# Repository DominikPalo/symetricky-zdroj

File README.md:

# Miniatúrny symetrický zdroj +/-5V, +/-12V s ochranou proti skratu

Repozitár obsahuje všetky potrebné iformácie k stavbe zdroja. Autorom elektro dizajnu (DPS a schéma) je David Čada (alias Davidus / Drirr90). Nakoľko sa jedná o šikovný zdroj pre domáce použite, v tomto repozitári nájdete dokumentáciu a materiály, ktoré som vytvoril pri jeho konštrukcii. Video s podrobným opisom zdroja nájdete na: https://youtu.be/iAIXDw9BsSQ.

## Obsah repozitára
1. Pôvodná schéma zapojenia a PCB vo formáte EAGLE (autor: David Čada)
1. Gerber súbory potrebné k výrobe DPS (JLCPCB, PCBWay, ...)
1. [Zoznam použitých komponentov (BOM)](BOM.md) aj s odkazmi na distribútorov TME a GME
1. 3D model krabičky na zdroj vhodný k tlači na 3D tlačiarni
1. Fotodokumetáciu mojej konštrukcie (pridám neskôr)

## Info od autora eletkro dizajnu:
>1. Pouze k nekomercnimu pouziti.
>1. Pokud chcete prezentovat zdroj i jinde, tak pouze s temito podminkami pouziti + odkaz na zdroj https://youtu.be/iAIXDw9BsSQ
>1. Rad zodpovim jakekoli dotazy na adrese cada.david zavinac gmail.com

## 3D krabička

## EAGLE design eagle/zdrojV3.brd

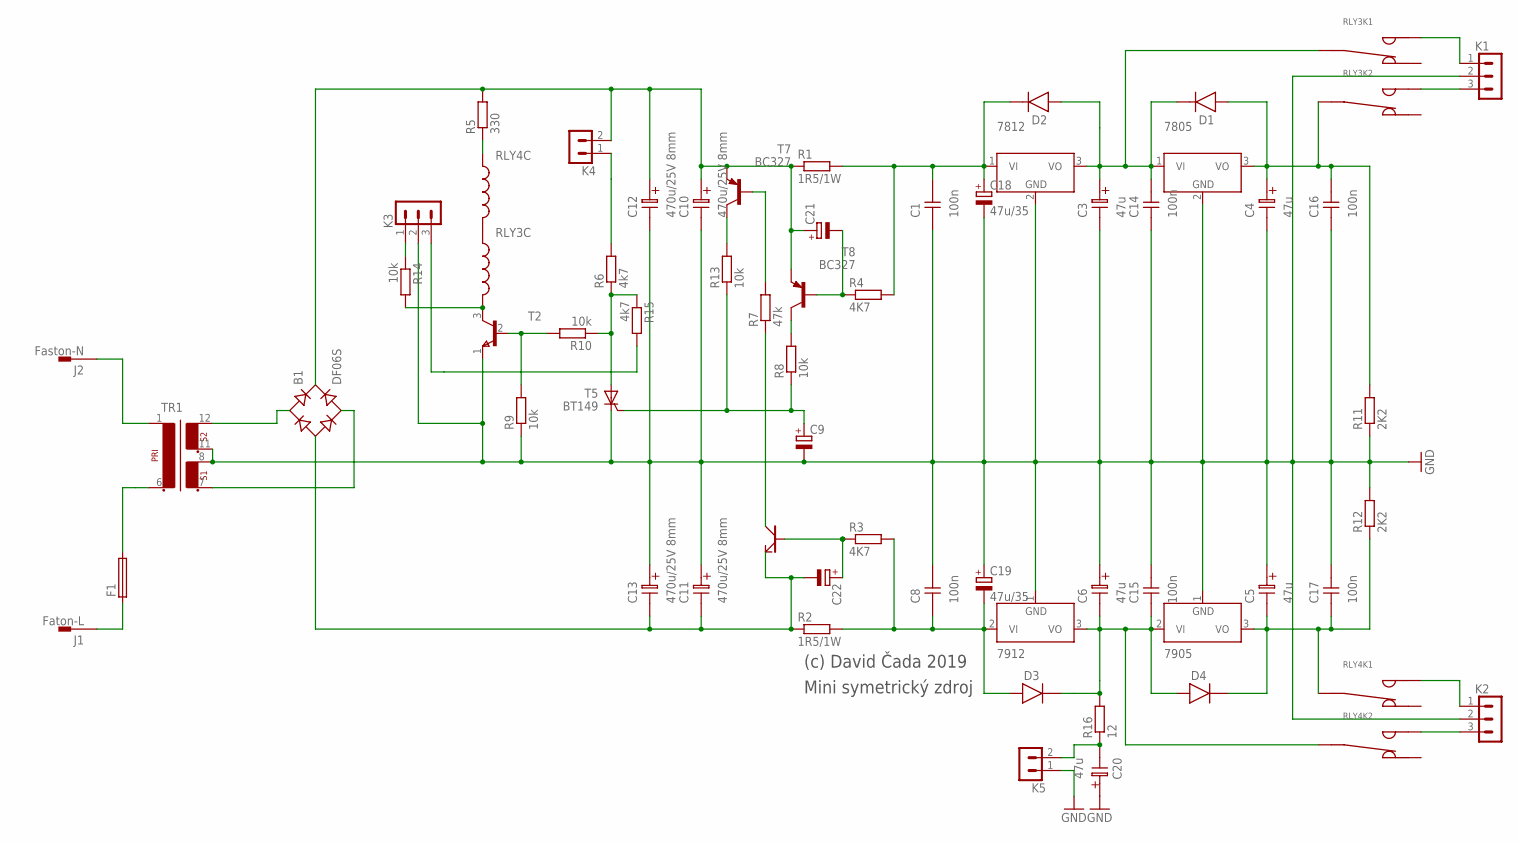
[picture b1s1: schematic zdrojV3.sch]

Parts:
7805: 7812; TO-220S
7812: 7805; TO-220S
7905: 7912; TO-220S
7912: 7905; TO-220S
B1: DF06S; DFS
C1, C8, C14, C15, C16, C17: 100n; CK
C3, C4, C5, C6, C20: 47u; CT12
C9, C21, C22: CPOL-EUE2.5-6; E2,5-6
C10, C11, C12, C13: 470u/25V 8mm; CT12
C18, C19: 47u/35; E2,5-6
D1, D2, D3, D4: 1N4007; DO41
F1: 19560
J1: Faton-L; F061.100
J2: Faston-N; F061.100
K1, K2, K3: PSH02-03P
K4, K5: PSH02-02P
R1, R2: 1R5/1W; 0411V
R3, R4: 4K7; 0207/2V
R5: 330; 0207/2V
R6, R15: 4k7; 0207/2V
R7: 47k; 0207/2V
R8, R9, R10, R13, R14: 10k; 0207/2V
R11, R12: 2K2; 0207/2V
R16: 12; 0207/2V
RLY3, RLY4: RELEG5V2; RG5V2
T2: BC337-40; TO-92C
T5: BT149; TO92-4
T6: MPSA44; TO92-EBC
T7, T8: BC327; TO92
TR1: EI48-2

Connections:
GND: 7805.2 (GND), 7812.2 (GND), 7905.1 (GND), 7912.1 (GND), C1.1, C3.2, C4.2, C5.1, C6.1, C8.2, C9.-, C10.2, C11.1, C12.2, C13.1, C14.1, C15.2, C16.1, C17.2, C18.-, C19.+, C20.1, K1.2, K2.2, K3.2, K5.1, R9.1, R11.1, R12.2, T2.1 (E), T5.C, TR1.8 (4), TR1.11 (5)
LEDGREEN+: K3.3, R15.2
unnamed: R7.2, T7.2 (B)
unnamed: 7805.1 (VI), 7812.3 (VO), C3.1, C14.2, D1.K, D2.A, RLY3.3
unnamed: 7905.2 (VI), 7912.3 (VO), C6.2, C15.1, D3.K, D4.A, R16.2, RLY4.6 (3)
unnamed: 7912.2 (VI), C8.1, C19.-, D3.A, R2.2, R3.2
unnamed: 7812.1 (VI), C1.2, C18.+, D2.K, R1.2, R4.2
unnamed: K1.1, RLY3.5 (1)
unnamed: 7905.3 (VO), C5.2, C17.1, D4.K, R12.1, RLY4.3
unnamed: R13.2, T7.3 (C)
unnamed: R9.2, R10.2, T2.2 (B)
unnamed: C22.+, R3.1, T6.B
unnamed: C21.-, R4.1, T8.2 (B)
unnamed: RLY3.1, RLY4.2
unnamed: R5.1, RLY4.1
unnamed: C9.+, R8.1, R13.1, T5.G
unnamed: R6.1, R10.1, R15.1, T5.A
unnamed: R14.2, RLY3.2, T2.3 (C)
unnamed: K4.1, R6.2
unnamed: K3.1, R14.1
unnamed: R7.1, T6.E (C)
unnamed: R8.2, T8.3 (C)
unnamed: F1.2, TR1.6 (2)
unnamed: B1.+, C10.1, C12.1, C21.+, K4.2, R1.1, R5.2, T7.1 (E), T8.1 (E)
unnamed: B1.AC1, TR1.12 (6)
unnamed: B1.AC2, TR1.7 (3)
unnamed: 7805.3 (VO), C4.1, C16.2, D1.A, R11.2, RLY3.6 (3)
unnamed: B1.-, C11.2, C13.2, C22.-, R2.1, T6.C (E)
unnamed: K1.3, RLY3.8 (1)
unnamed: K2.1, RLY4.5 (1)
unnamed: K2.3, RLY4.8 (1)
unnamed: C20.2, K5.2, R16.1
unnamed: J2.A1, J2.A2, TR1.1
POJISTKA: F1.1, J1.A1, J1.A2

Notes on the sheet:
(c) David Čada 2019
Mini symetrický zdroj

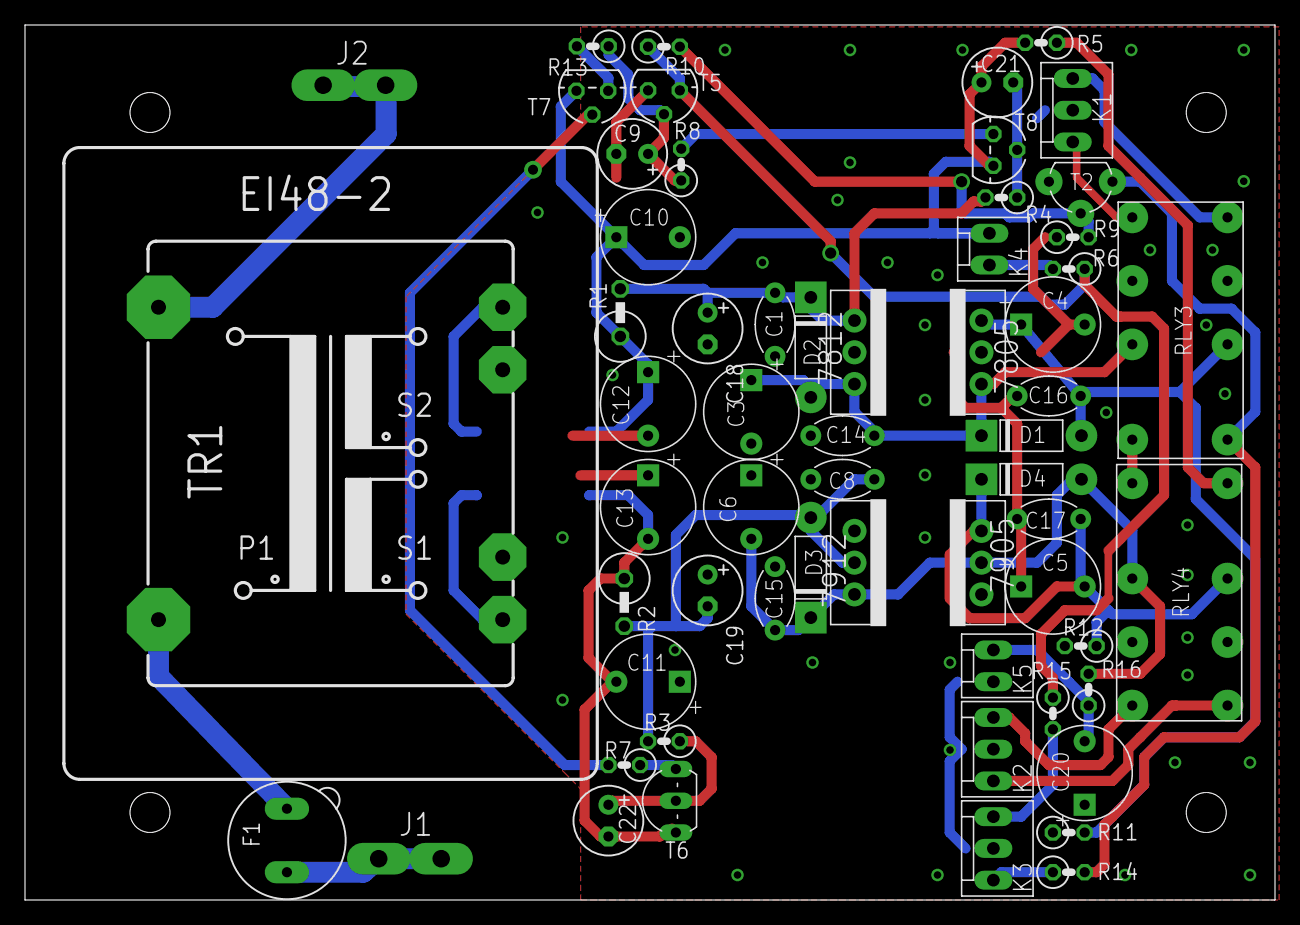
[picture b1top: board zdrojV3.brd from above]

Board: 2 copper layers, 100.0 x 70.0 mm, 61 parts (1 on the bottom side), 34 nets.

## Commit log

2021-01-23 Add README and BOM
2021-01-24 Add EAGLE files
2021-01-24 Add gerber files
2021-01-24 Add packages, capacitors and resistors to the BOM
2021-02-06 Add missing GME items
2021-03-13 Add case STL files
2021-03-13 Add C9, C21, C22 to BOM
2021-03-13 Fix 123-093 GME URL

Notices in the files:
eagle/zdrojV3.brd:
(c) 2012 David Cada (@Drirr90)
parts and their libraries:
Copyright (C) PaJa 2011
